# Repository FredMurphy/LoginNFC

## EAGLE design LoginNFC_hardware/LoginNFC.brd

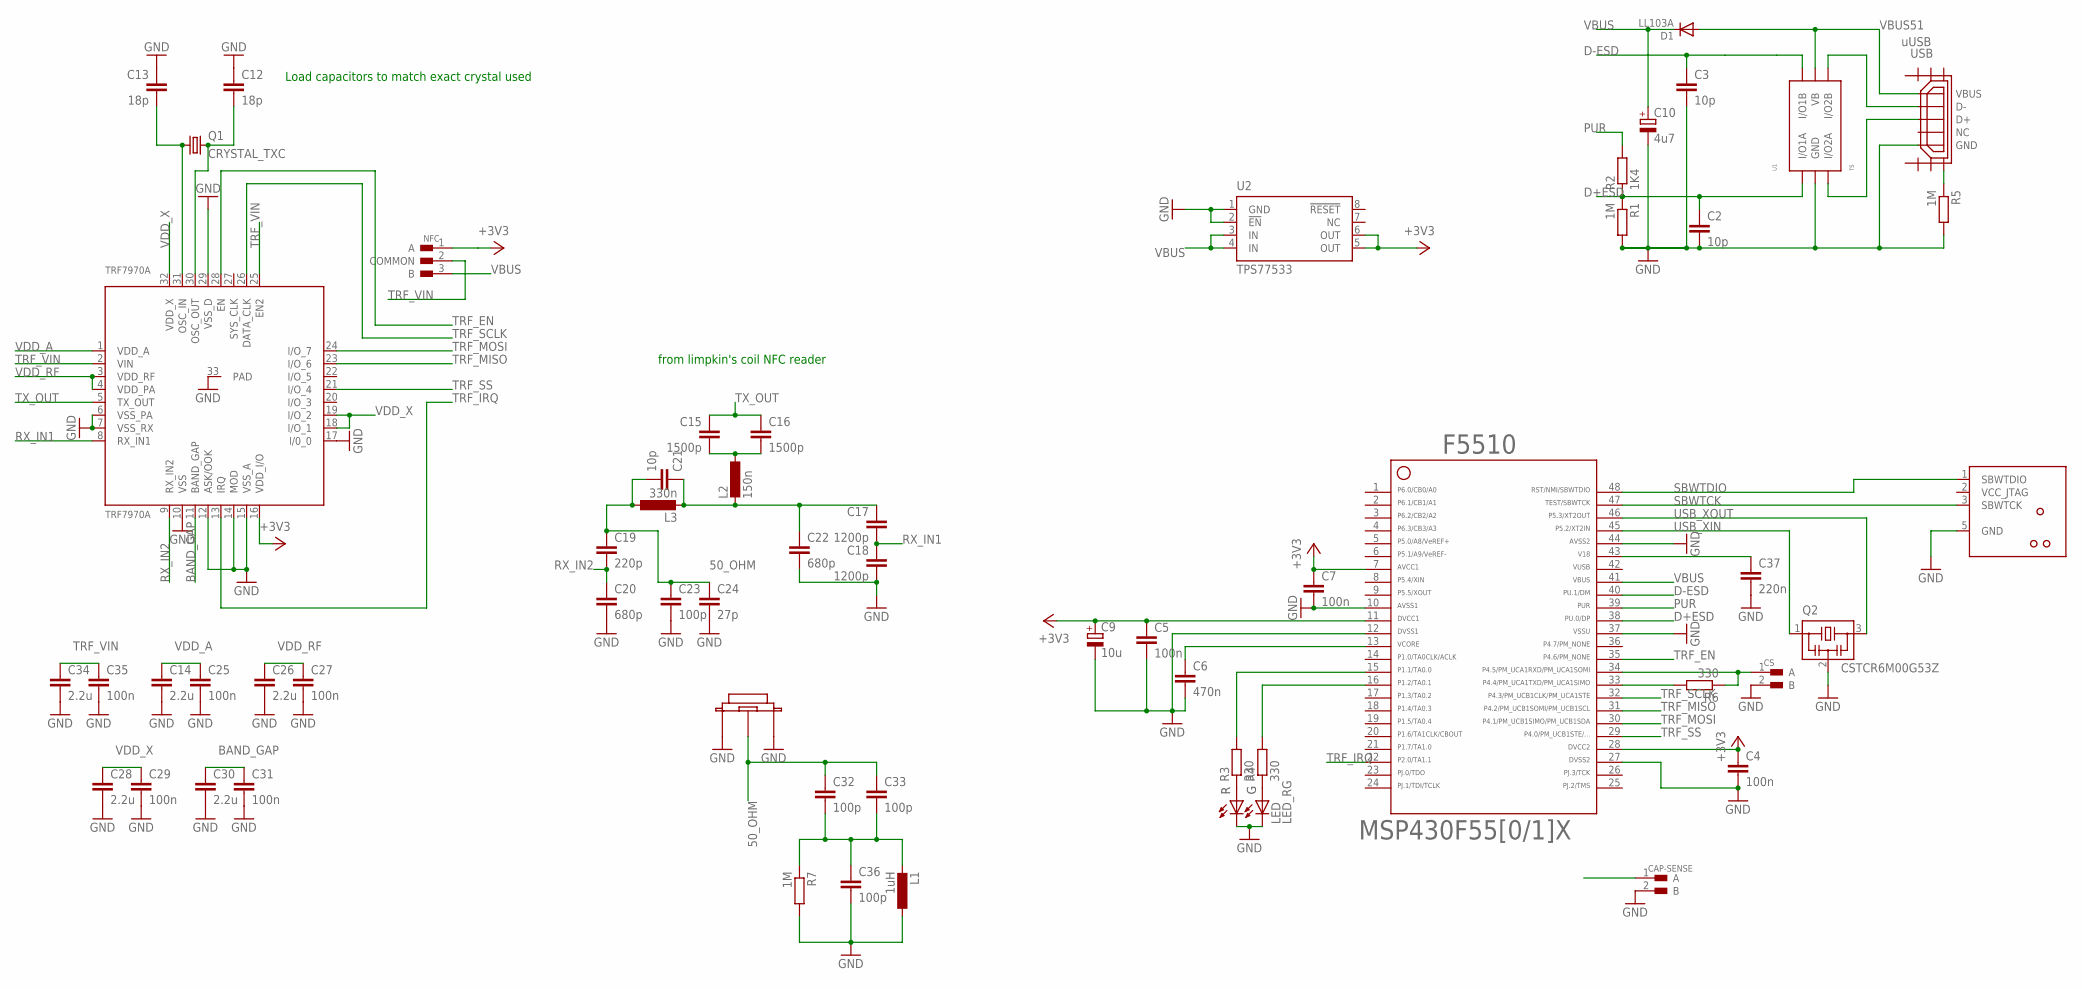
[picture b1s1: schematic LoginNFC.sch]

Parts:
C2, C3, C21: 10p; C0805
C4, C5, C7, C25, C27, C29, C31, C35: 100n; C0805
C6: 470n; C0805
C9: 10u; A/3216-18R
C10: 4u7; A/3216-18R
C12, C13: 18p; C0805
C14, C26, C28, C30, C34: 2.2u; C0805
C15, C16: 1500p; C0805
C17, C18: 1200p; C0805
C19: 220p; C0805
C20, C22: 680p; C0805
C23, C32, C33, C36: 100p; C0805
C24: 27p; C0805
C37: 220n; C0805
CAP-SENSE: PAD; JUMP-2
CS: PAD; JUMP-2
D1: LL103A; SOD-80
F5510: F55[0/1]X---PT48; PT48
JTAG: TC2030-MSP430-NO-UART-NL; TC2030-MSP430-NL-NO-UART
L1: 1uH; RADIAL_MIDMOUNT_5
L2: 150n; L1008
L3: 330n; L1008
LED: LED_RG; 1411
NFC: JUMPER; SMT-JUMPER
Q1: CRYSTAL_TXC; CRYSTAL_TCX
Q2: CSTCR6M00G53Z; CSTCR6M
R1, R5, R7: 1M; R0805
R2: 1K4; R0805
R3, R4, R6: 330; R0805
TRF7970A: TRF7970A; QFN(RHB)32
U1: TS; SOT-457
U2: TPS77533; SO08
UFL1: U.FL
USB: uUSB; HIROSE-ZX62R-B-5P

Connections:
42: F5510.42
50_OHM: C19.1, C21.2, C23.1, C24.1, C32.1, C33.1, L3.1, UFL1.RF
+3V3: C4.1, C5.1, C7.1, C9.+, F5510.7, F5510.11, F5510.28, NFC.1 (A), TRF7970A.16 (VDD_I/O), U2.5 (OUT), U2.6 (OUT)
BAND_GAP: C30.1, C31.1, TRF7970A.11 (BAND_GAP)
D+ESD: C2.1, F5510.38, R1.1, R2.1, U1.1 (I/O1A)
D-ESD: C3.1, F5510.40, U1.6 (I/O1B)
GND: C2.2, C3.2, C4.2, C5.2, C6.2, C7.2, C9.-, C10.-, C12.1, C13.1, C14.2, C18.2, C20.2, C22.2, C23.2, C24.2, C25.2, C26.2, C27.2, C28.2, C29.2, C30.2, C31.2, C34.2, C35.2, C36.2, C37.2, CAP-SENSE.2 (B), CS.2 (B), F5510.10, F5510.12, F5510.27, F5510.37, F5510.44, JTAG.5 (GND), L1.P$1 (1), LED.P$3 (RED_C), LED.P$4 (GREEN_C), Q2.2, R1.2, R5.2, R7.2, TRF7970A.6 (VSS_PA), TRF7970A.7 (VSS_RX), TRF7970A.10 (VSS), TRF7970A.12 (ASK/OOK), TRF7970A.14 (MOD), TRF7970A.15 (VSS_A), TRF7970A.17 (I/0_0), TRF7970A.29 (VSS_D), TRF7970A.33 (PAD), U1.2 (GND), U2.1 (GND), U2.2 (!EN), UFL1.GND1, UFL1.GND2, USB.GND
LED_G: F5510.16, R4.2
LED_R: F5510.15, R3.2
unnamed: U1.3 (I/O2A), USB.D+
unnamed: U1.4 (I/O2B), USB.D-
unnamed: C6.1, F5510.13
unnamed: LED.P$1 (RED_A), R3.1
unnamed: LED.P$2 (GREEN_A), R4.1
unnamed: C32.2, C33.2, C36.1, L1.P$2 (2), R7.1
unnamed: R5.1, USB.SHIELD3
unnamed: C15.2, C16.2, L2.1
unnamed: C17.1, C21.1, C22.1, L2.2, L3.2
unnamed: CS.1 (A), F5510.34, R6.1
unnamed: C13.2, Q1.1, TRF7970A.31 (OSC_IN)
unnamed: C12.2, Q1.2, TRF7970A.30 (OSC_OUT)
unnamed: F5510.33, R6.2
PUR: F5510.39, R2.2
RX_IN1: C17.2, C18.1, TRF7970A.8 (RX_IN1)
RX_IN2: C19.2, C20.1, TRF7970A.9 (RX_IN2)
SBWTCK: F5510.47, JTAG.3 (SBWTCK)
SBWTDIO: F5510.48, JTAG.1 (SBWTDIO)
TRF_EN: F5510.35, TRF7970A.28 (EN)
TRF_IRQ: F5510.22, TRF7970A.13 (IRQ)
TRF_MISO: F5510.31, TRF7970A.23 (I/O_6)
TRF_MOSI: F5510.30, TRF7970A.24 (I/O_7)
TRF_SCLK: F5510.32, TRF7970A.26 (DATA_CLK)
TRF_SS: F5510.29, TRF7970A.21 (I/O_4)
TRF_VIN: C34.1, C35.1, NFC.2 (COMMON), TRF7970A.2 (VIN), TRF7970A.25 (EN2)
TX_OUT: C15.1, C16.1, TRF7970A.5 (TX_OUT)
USB_XIN: F5510.45, Q2.1
USB_XOUT: F5510.46, Q2.3
V18: C37.1, F5510.43
VBUS: C10.+, D1.2 (K), F5510.41, NFC.3 (B), U2.3 (IN), U2.4 (IN)
VBUS51: D1.1 (A), U1.5 (VB), USB.VBUS
VCC_JTAG: JTAG.2 (VCC_JTAG)
VDD_A: C14.1, C25.1, TRF7970A.1 (VDD_A)
VDD_RF: C26.1, C27.1, TRF7970A.3 (VDD_RF), TRF7970A.4 (VDD_PA)
VDD_X: C28.1, C29.1, TRF7970A.18 (I/O_1), TRF7970A.19 (I/O_2), TRF7970A.32 (VDD_X)

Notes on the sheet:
from limpkin's coil NFC reader
Load capacitors to match exact crystal used

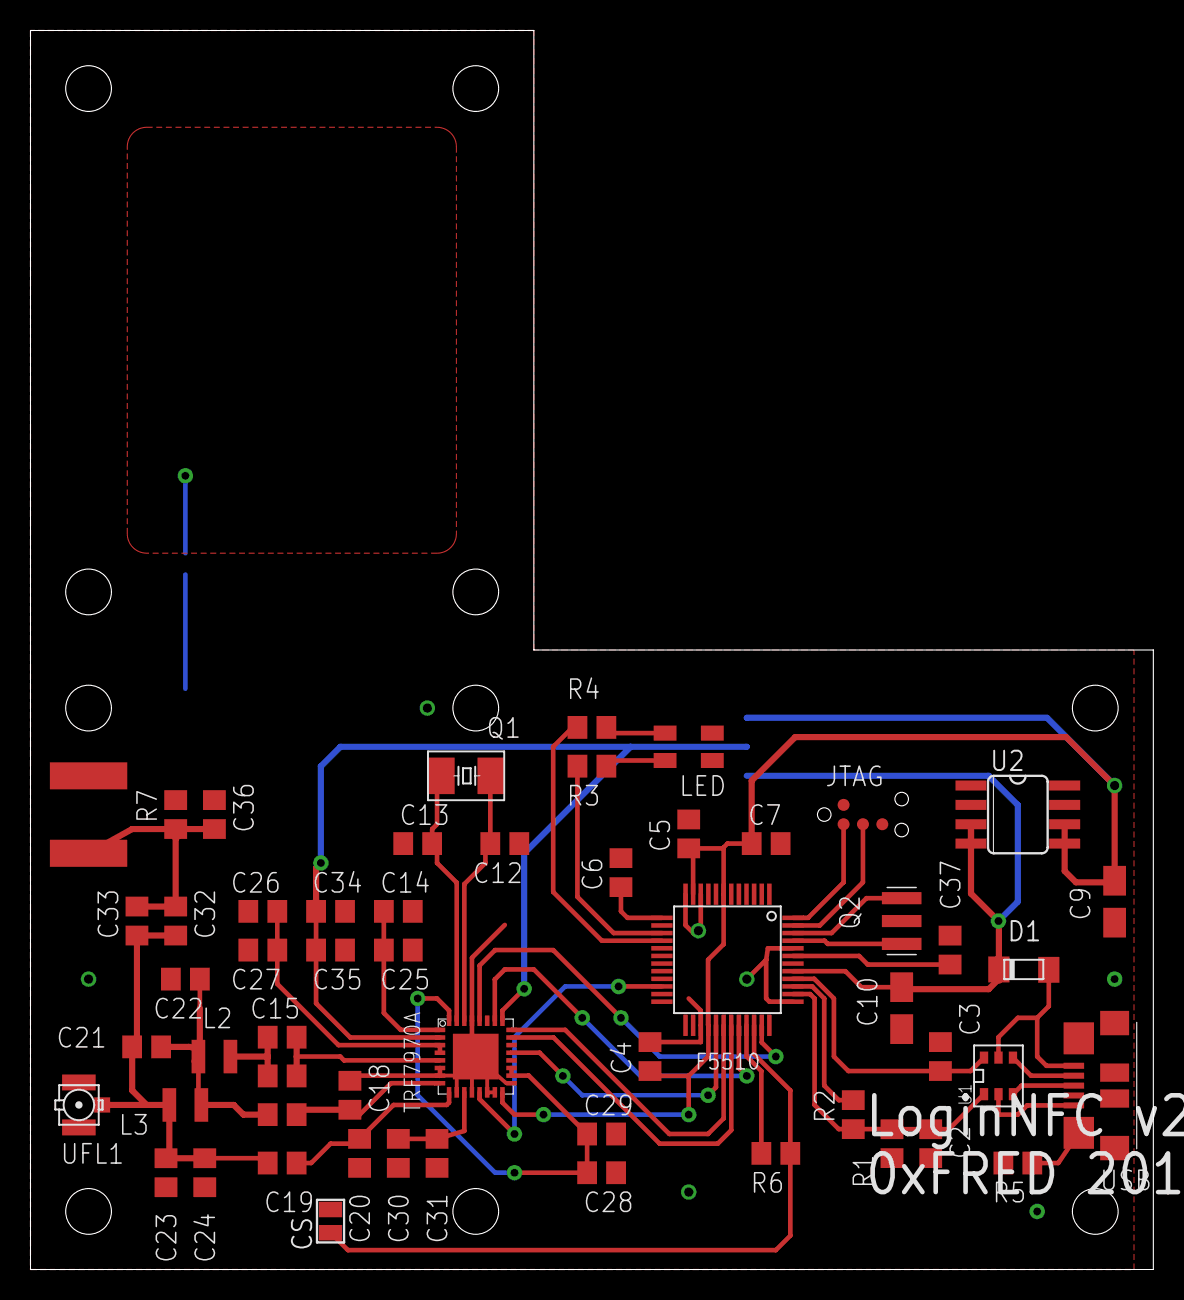
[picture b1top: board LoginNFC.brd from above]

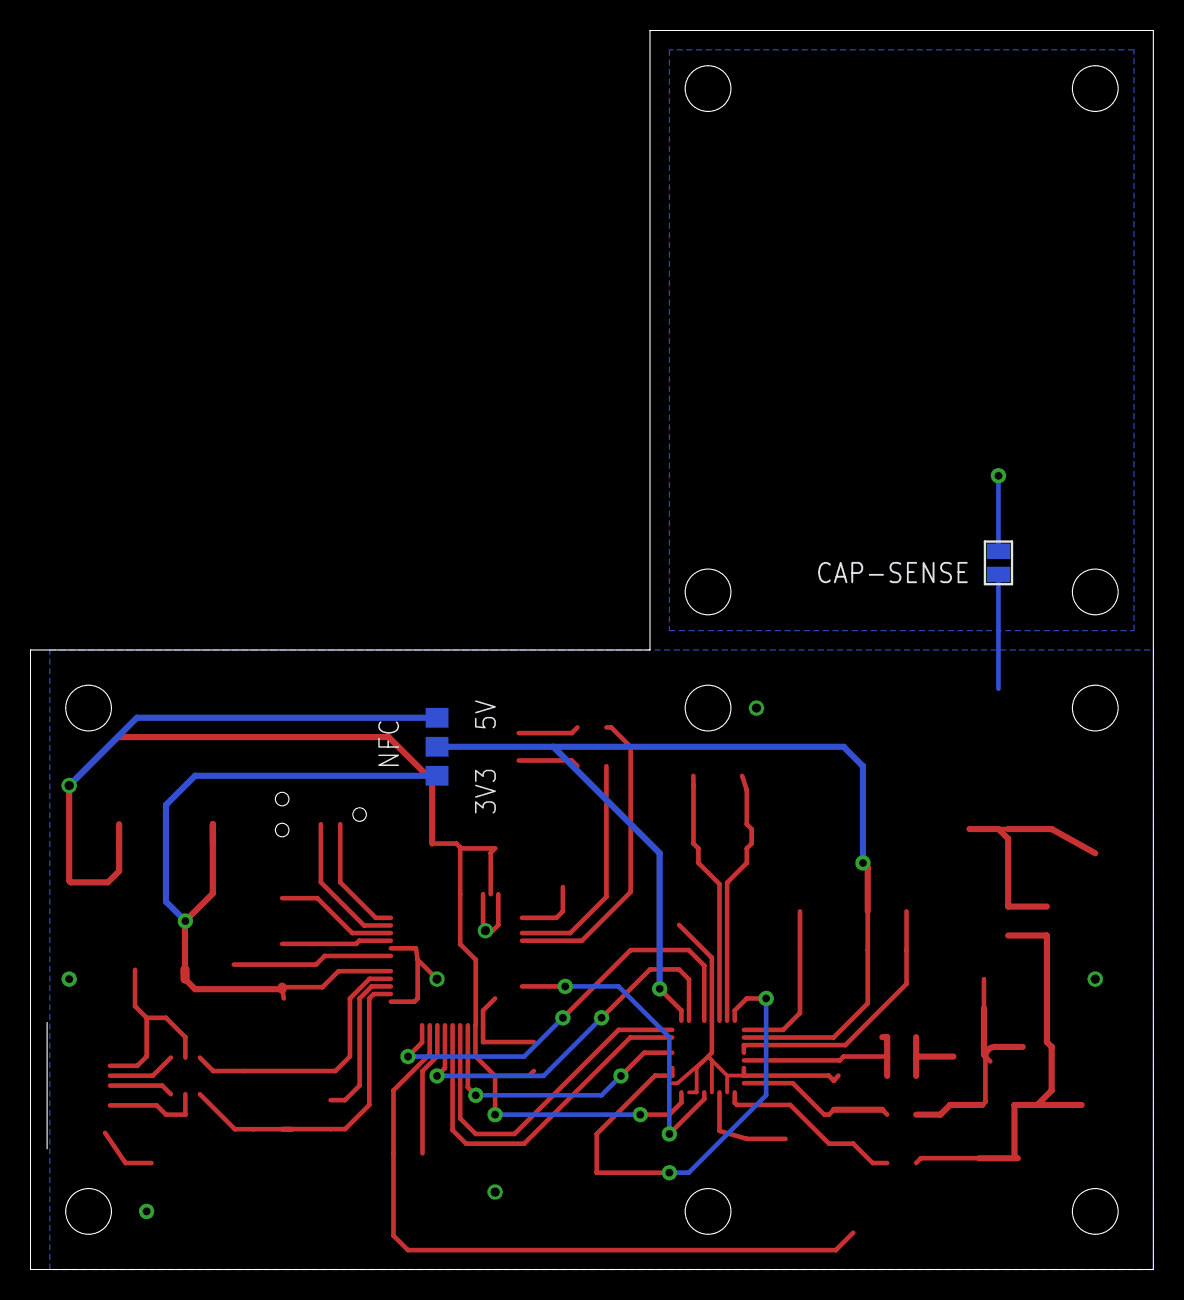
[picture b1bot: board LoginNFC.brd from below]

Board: 2 copper layers, 73.7 x 81.3 mm, 58 parts (2 on the bottom side), 42 nets.

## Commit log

2016-02-19 Initial commit of version 2.1 - both hardware and software
2016-02-21 Corrected accidentally unchecked 'manage target configuration'
2016-02-21 Updated compiler version
2016-02-22 Scan to set new password and NFC tag ID
2016-02-23 Initial pass at case (inches)
2016-02-28 Updated to CamBam case files
2016-04-04 Added start of Dell monitor mount
2016-11-05 Changes to CNC milled case. Added 3D printed monitor mount
2016-11-08 Added PxIN(port) macros
2016-11-11 Added working CapTouch - independent of NFC functionality
2016-11-14 Successful integration of cap touch. Won't work at all without it though...
2016-11-14 Some tidying only
2016-11-17 Better sensitivity for CapTouch
2018-01-23 Optional CapTouch
2018-02-09 Tweaked scan time. Pause after storing new password.
2018-02-17 Improved serial console UI and added Linux mode

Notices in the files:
parts and their libraries:
tag-connect: ©2009 ROFA.cz - modified and updated by Robert Darlington ‹rdarlington@gmail.com›
